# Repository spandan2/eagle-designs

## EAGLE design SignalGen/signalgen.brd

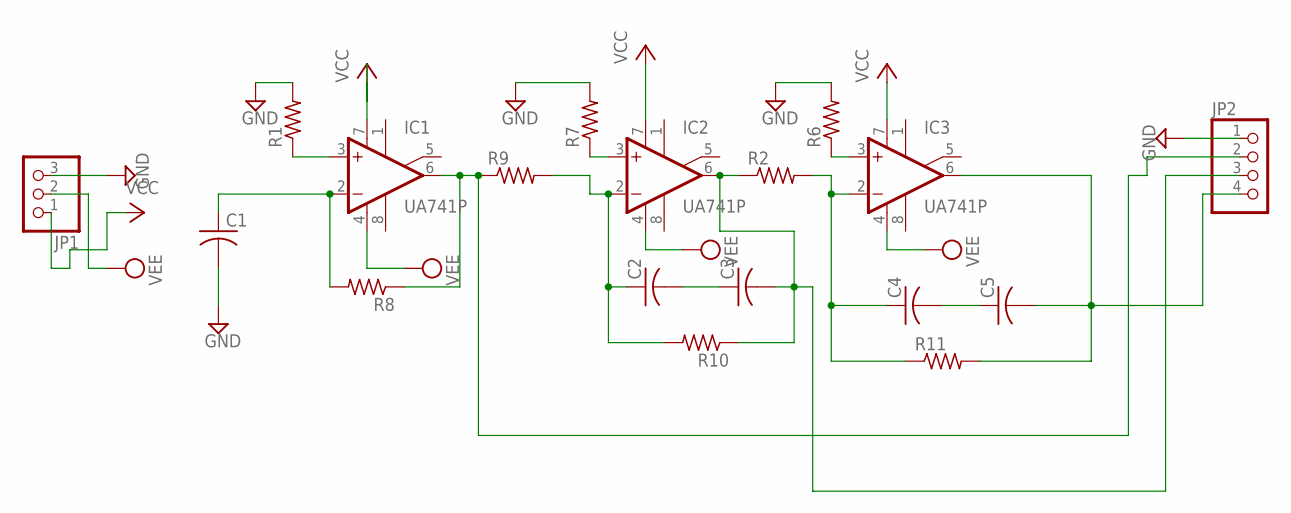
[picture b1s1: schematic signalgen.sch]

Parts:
C1, C2, C3, C4, C5: C-US050-024X044; C050-024X044
IC1, IC2, IC3: UA741P; DIL08
JP1: PINHD-1X3; 1X03
JP2: PINHD-1X4; 1X04
R1, R2, R6, R7, R8, R9, R10, R11: R-US_0207/10; 0207/10

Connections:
GND: C1.2, JP1.3, JP2.1, R1.2, R6.2, R7.2
unnamed: C1.1, IC1.2 (-IN), R8.2
unnamed: IC1.6 (OUT), JP2.2, R8.1, R9.1
unnamed: C2.1, IC2.2 (-IN), R9.2, R10.2
unnamed: C4.2, C5.1
unnamed: C2.2, C3.1
unnamed: C3.2, IC2.6 (OUT), JP2.3, R2.1, R10.1
unnamed: C4.1, IC3.2 (-IN), R2.2, R11.1
unnamed: IC1.3 (+IN), R1.1
unnamed: IC2.3 (+IN), R7.1
unnamed: IC3.3 (+IN), R6.1
unnamed: C5.2, IC3.6 (OUT), JP2.4, R11.2
VCC: IC1.7 (V+), IC2.7 (V+), IC3.7 (V+), JP1.1
VEE: IC1.4 (V-), IC2.4 (V-), IC3.4 (V-), JP1.2

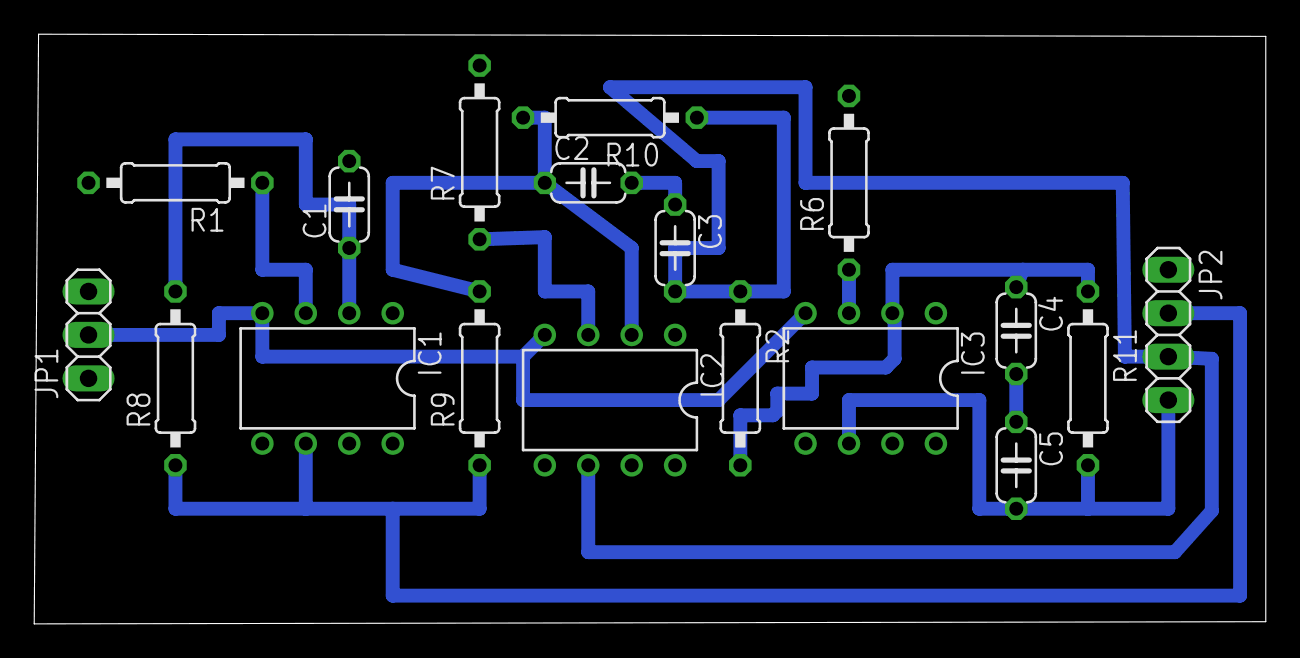
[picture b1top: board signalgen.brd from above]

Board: 2 copper layers, 72.0 x 34.5 mm, 18 parts (0 on the bottom side), 14 nets.

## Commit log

2017-10-07 Adding designs
